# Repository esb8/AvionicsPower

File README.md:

## Overview

This project is a custom RP2040-based **Power Distribution Board**, designed for use in an avionics stack comprising three CAN-connected PCBs:  
- Sensor Board  
- Power Distribution Board **(this board)** 
- GPS Board

The system is intended for **high-power model rocketry**, and this board’s primary role is to **distribute power** to the rest of the system while also managing essential subsystems such as communication, monitoring, and recovery signaling.

---

## 📡 PCB Features

- High-current 3.3 V synchronous buck converter (up to 3 A), operating at 1.5 MHz and ~95% efficiency  
- Low-noise LDO with 60 dB PSRR @ 100 Hz, delivering up to 500 mA at 3.3 V  
- Single-cell Li-ion/LiPo battery protection IC with over-voltage, under-voltage, and over-current protection  
- CAN controller and transceiver  
- RP2040 microcontroller  
- USB-C interface  
- Onboard status LEDs for buck converter, MCU status, and USB-C diagnostics  
- External 128 Mbit W25Q128JVS flash memory  
- MAX98357A I²S digital amplifier connected to a speaker for audible recovery

---

## ✅ PCB Design Criteria

This board was designed to meet the following system-level criteria:

- **Stable, low-noise 3.3 V rail** for analog/digital loads — supports up to 500 mA with minimal line/load regulation (target: ±0.1%)
- **High-current 3.3 V rail** capable of supplying up to 3 A to downstream PCBs
- **Battery protection** for a 1S LiPo cell, including self-recovery from under-voltage and short-circuit protection
- **CAN bus communication interface** to enable modular system design with multiple nodes
- **Audible recovery system** — implemented using the **MAX98357A I²S Class-D amplifier**, which drives a speaker directly from the RP2040 using digital audio

---

## 📷 Media

**Schematic**  

**PCB Layout**  

**3D Model**

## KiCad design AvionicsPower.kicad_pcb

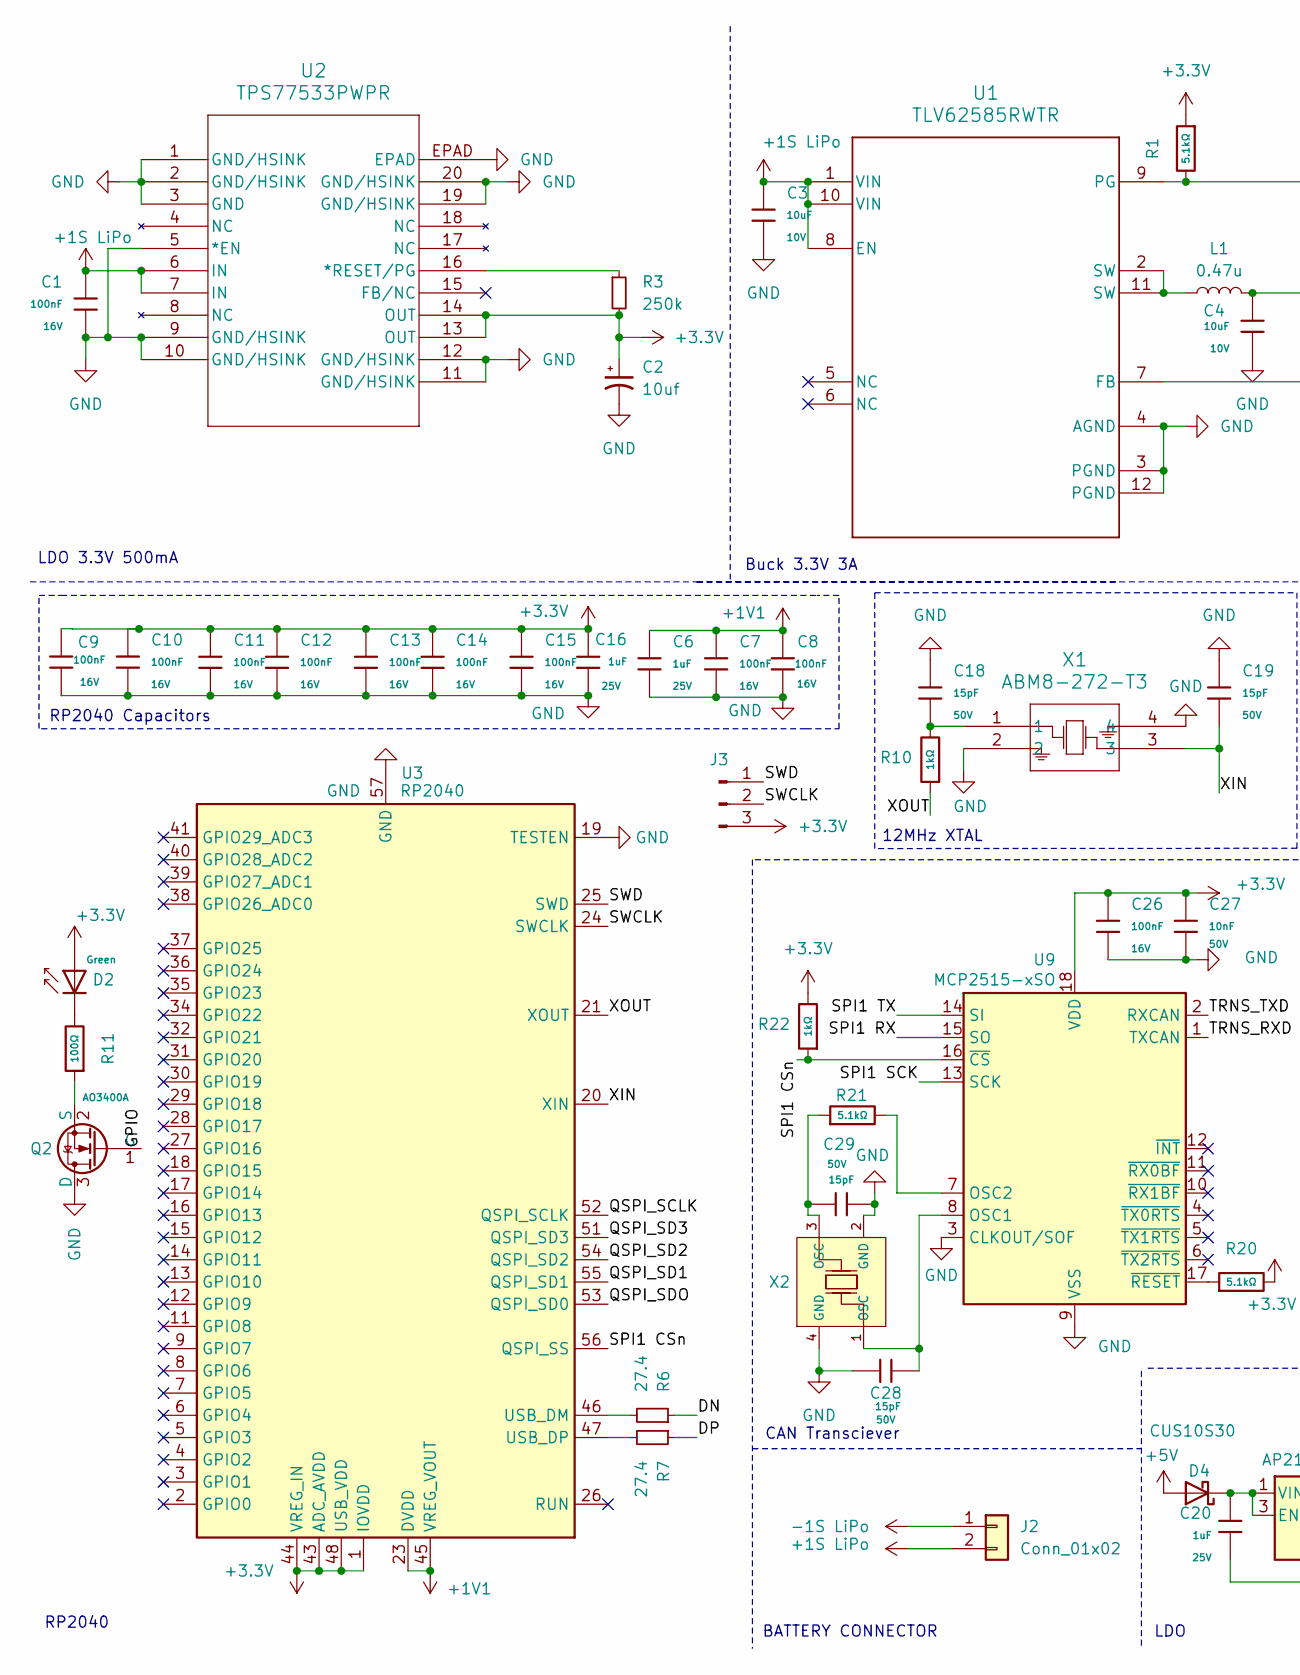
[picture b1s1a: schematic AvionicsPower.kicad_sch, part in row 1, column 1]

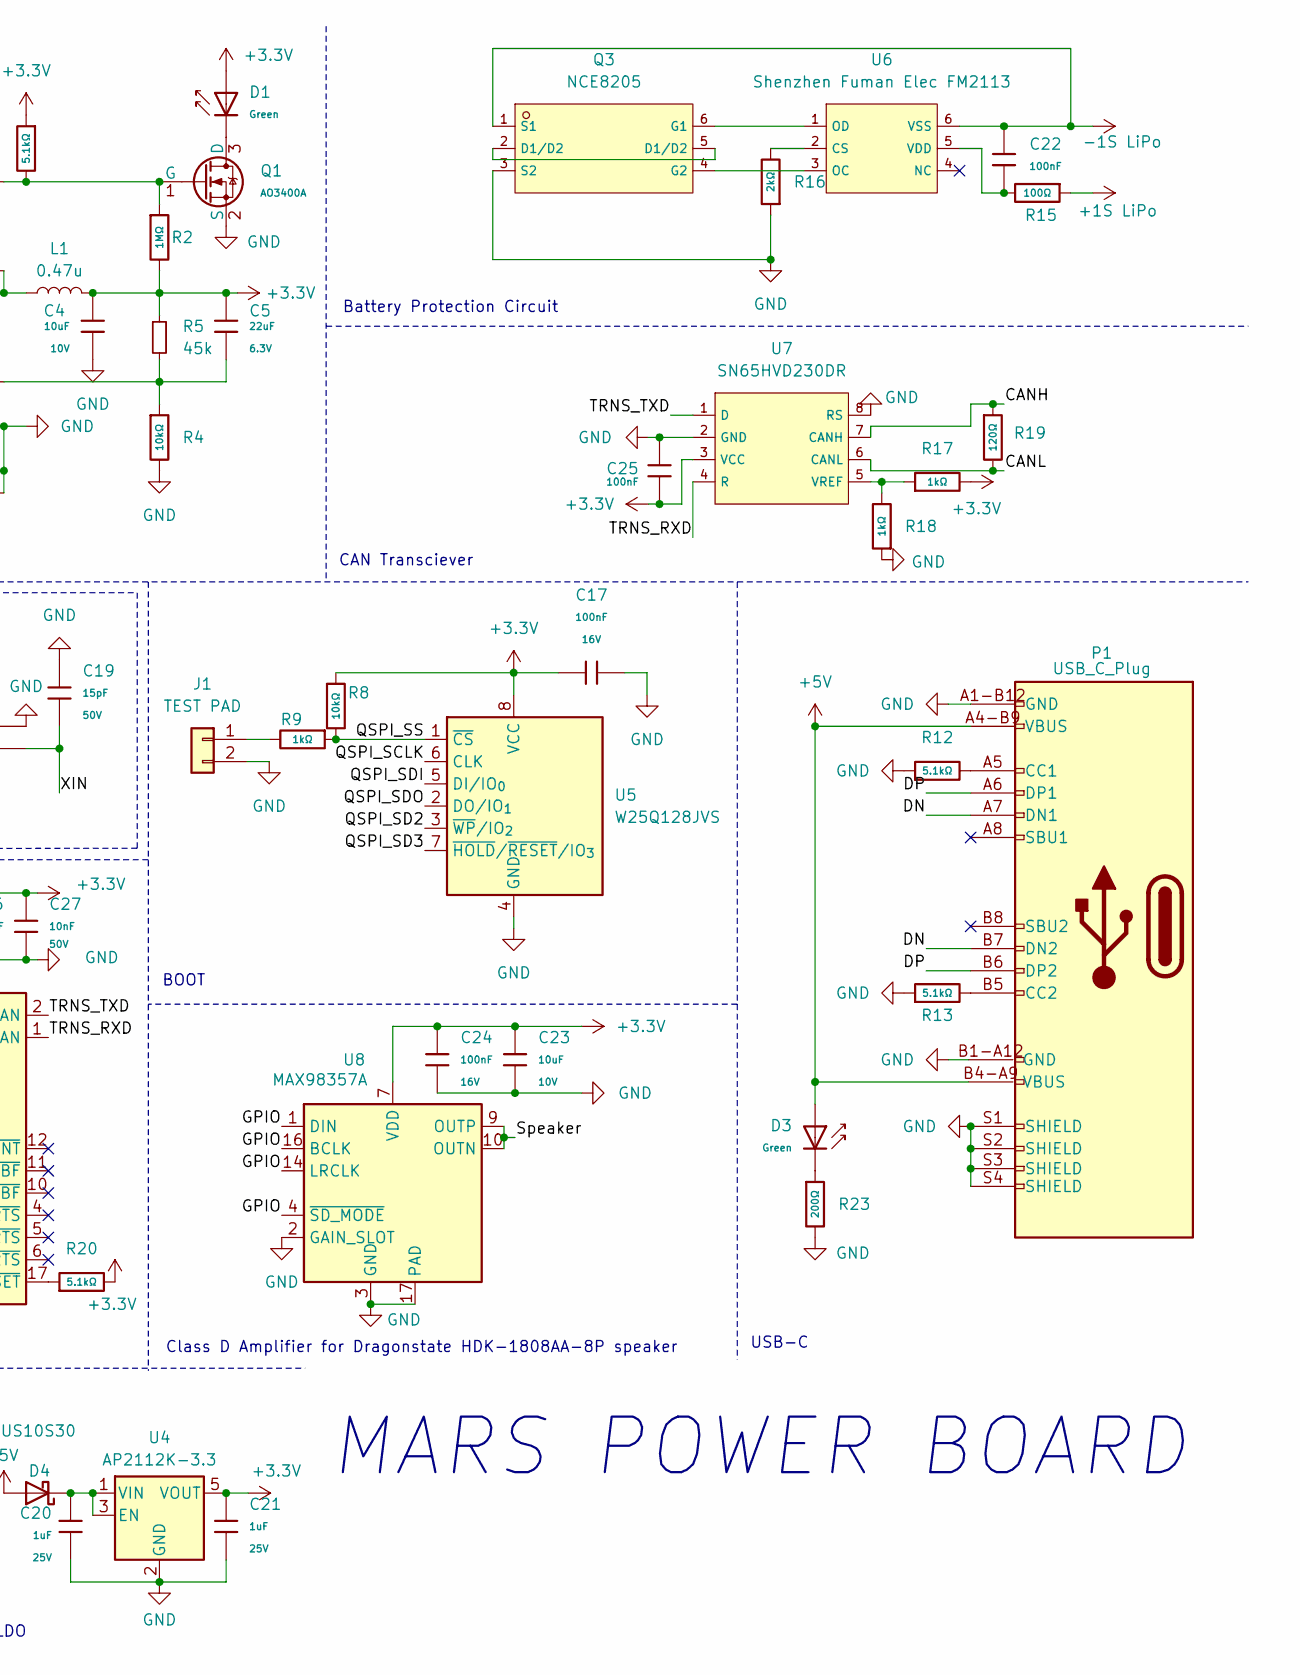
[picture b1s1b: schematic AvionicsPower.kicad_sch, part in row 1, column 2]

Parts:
C1, C7, C8, C9, C10, C11, C12, C13, C14, C15, C17, C22, C24, C25, C26: 100nF; C_0402; Voltage Rated 16V; Tolerance ±10%; Part CL05B104KO5NNNC; LCSC C1525
C2: 10uf; C_0805; LCSC C696821
C3, C4, C23: 10uF; C_0603; Voltage Rated 10V; Tolerance ±10%; Part CL10A106KP8NNNC; LCSC C19702
C5: 22uF; C_0603; Voltage Rated 6.3V; Tolerance ±20%; Part CL10A226MQ8NRNC; LCSC C59461
C6, C16, C20, C21: 1uF; C_0402; Voltage Rated 25V; Tolerance ±10%; Part CL05A105KA5NQNC; LCSC C52923
C18, C19, C28, C29: 15pF; C_0402; Voltage Rated 50V; Tolerance ±5%; Part 0402CG150J500NT; LCSC C1548
C27: 10nF; C_0402; Voltage Rated 50V; Tolerance ±10%; Part CL05B103KB5NNNC; LCSC C15195
D1, D2, D3: Green; D_0805; Part KT-0805G; LCSC C2297
D4: CUS10S30; D_SOD-323; LCSC C146335
J1: TEST PAD
J2: Conn_01x02; AMASS_XT60PW-M_1x02_P7.20mm_Horizontal; LCSC C131337
J3: Conn_01x03_Pin
L1: 0.47u
P1: USB_C_Plug; USB_C_Receptacle_GCT_USB4105-xx-A_16P_TopMnt_Horizontal
Q1, Q2: AO3400A; Q_SOT-23; Part AO3400A; LCSC C20917
Q3: NCE8205; SOT-23-6_L2.9-W1.6-P0.95-LS2.8-BR; LCSC C502858
R1, R12, R13, R20, R21: 5.1kΩ; R_0402_1005Metric; Overload Voltage (Max) 50V; Tolerance ±1%; Part 0402WGF5101TCE; LCSC C25905
R2: 1MΩ; R_0603_1608Metric; Overload Voltage (Max) 75V; Tolerance ±1%; Part 0603WAF1004T5E; LCSC C22935
R3: 250k; R_1206; LCSC C2828893
R4: 10kΩ; R_0805; Overload Voltage (Max) 150V; Tolerance ±1%; Part 0805W8F1002T5E; LCSC C17414
R5: 45k
R6, R7: 27.4; C_0402_1005Metric; LCSC C850920
R8: 10kΩ; R_0402_1005Metric; Overload Voltage (Max) 50V; Tolerance ±1%; Part 0402WGF1002TCE; LCSC C25744
R9, R10, R17, R18, R22: 1kΩ; R_0402_1005Metric; Overload Voltage (Max) 50V; Tolerance ±1%; Part 0402WGF1001TCE; LCSC C11702
R11, R15: 100Ω; R_0402_1005Metric; Overload Voltage (Max) 50V; Tolerance ±1%; Part 0402WGF1000TCE; LCSC C25076
R16: 2kΩ; R_0402_1005Metric; Overload Voltage (Max) 50V; Tolerance ±1%; Part 0402WGF2001TCE; LCSC C4109
R19: 120Ω; R_0402_1005Metric; Overload Voltage (Max) 50V; Tolerance ±1%; Part 0402WGF1200TCE; LCSC C25079
R23: 200Ω; R_0402; Overload Voltage (Max) 50V; Tolerance ±1%; Part 0402WGF2000TCE; LCSC C25087
U1: TLV62585RWTR; RWT0012A
U2: TPS77533PWPR; PWP20_3P38X2P4
U3: RP2040; QFN-56-1EP_7x7mm_P0.4mm_EP3.2x3.2mm
U4: AP2112K-3.3; SOT-23-5
U5: W25Q128JVS; SOIC-8_5.3x5.3mm_P1.27mm
U6: Shenzhen Fuman Elec FM2113; SOT-23-6_L2.9-W1.6-P0.95-LS2.8-BL; LCSC C2832124
U7: SN65HVD230DR; SOIC-8_L4.9-W3.9-P1.27-LS6.0-BL; Supply Voltage 3V~3.6V; Part SN65HVD230DR; LCSC C12084
U8: MAX98357A; TQFN-16-1EP_3x3mm_P0.5mm_EP1.23x1.23mm
U9: MCP2515-xSO; QFN-20-1EP_4x4mm_P0.5mm_EP2.5x2.5mm
X1: ABM8-272-T3; Crystal_SMD_3225-4Pin_3.2x2.5mm
X2: X322512MSB4SI; CRYSTAL-SMD_4P-L3.2-W2.5-BL; Frequency Tolerance ±10ppm; Part X322512MSB4SI; LCSC C9002

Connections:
+1S LiPo: C1.1, C3.1, J2.2, R15.1, U1.1 (VIN), U1.8 (EN), U1.10 (VIN), U2.6 (IN), U2.7 (IN)
+1V1: C6.1, C7.1, C8.1, U3.23 (DVDD), U3.45 (VREG_VOUT), U3.50 (DVDD)
+3.3V: C2.1, C4.1, C5.1, C9.1, C10.1, C11.1, C12.1, C13.1, C14.1, C15.1, C16.1, C17.1, C21.1, C23.1, C24.1, C25.2, C26.1, C27.1, D1.2, D2.2, J3.3, L1.2, R1.1, R2.2, R3.2, R5.1, R8.1, R17.2, R20.2, R22.2, U2.13 (OUT), U2.14 (OUT), U3.1 (IOVDD), U3.10 (IOVDD), U3.22 (IOVDD), U3.33 (IOVDD), U3.42 (IOVDD), U3.43 (ADC_AVDD), U3.44 (VREG_IN), U3.48 (USB_VDD), U3.49 (IOVDD), U4.5 (VOUT), U5.8 (VCC), U7.3 (VCC), U8.7 (VDD), U8.8 (VDD), U9.18 (VDD)
+5V: D3.2, D4.2 (A), P1.A4-B9 (VBUS), P1.B4-A9 (VBUS)
-1S LiPo: C22.1, J2.1, Q3.1 (S1), U6.6 (VSS)
/CANH: R19.1, U7.7 (CANH)
/CANL: R19.2, U7.6 (CANL)
/DN: P1.A7 (DN1), P1.B7 (DN2), R6.1
/DP: P1.A6 (DP1), P1.B6 (DP2), R7.1
/GPIO: Q2.1 (G), U8.1 (DIN), U8.4 (~SD_MODE), U8.14 (LRCLK), U8.16 (BCLK)
/QSPI_SCLK: U3.52 (QSPI_SCLK), U5.6 (CLK)
/QSPI_SD1: U3.55 (QSPI_SD1)
/QSPI_SD2: U3.54 (QSPI_SD2), U5.3 (~WP/IO_{2})
/QSPI_SD3: U3.51 (QSPI_SD3), U5.7 (~HOLD/~RESET/IO_{3})
/QSPI_SDI: U5.5 (DI/IO_{0})
/QSPI_SDO: U3.53 (QSPI_SD0), U5.2 (DO/IO_{1})
/QSPI_SS: R8.2, R9.1, U5.1 (~CS)
/SPI1 CSn: R22.1, U3.56 (QSPI_SS), U9.16 (~CS)
/SPI1 RX: U9.15 (SO)
/SPI1 SCK: U9.13 (SCK)
/SPI1 TX: U9.14 (SI)
/SWCLK: J3.2, U3.24 (SWCLK)
/SWD: J3.1, U3.25 (SWD)
/Speaker: U8.9 (OUTP), U8.10 (OUTN)
/TRNS_RXD: U7.4 (R), U9.1 (TXCAN)
/TRNS_TXD: U7.1 (D), U9.2 (RXCAN)
/XIN: C19.2, U3.20 (XIN), X1.3
/XOUT: R10.1, U3.21 (XOUT)
GND: C1.2, C2.2, C3.2, C4.2, C6.2, C7.2, C8.2, C9.2, C10.2, C11.2, C12.2, C13.2, C14.2, C15.2, C16.2, C17.2, C18.1, C19.1, C20.1, C21.2, C23.2, C24.2, C25.1, C26.2, C27.2, C28.1, C29.1, J1.2, P1.A1-B12 (GND), P1.B1-A12 (GND), P1.S1 (SHIELD), P1.S2 (SHIELD), P1.S3 (SHIELD), P1.S4 (SHIELD), Q1.2 (S), Q2.3 (D), Q3.3 (S2), R4.2, R12.1, R13.1, R16.1, R18.1, R23.2, U1.3 (PGND), U1.4 (AGND), U1.12 (PGND), U2.1 (GND/HSINK), U2.2 (GND/HSINK), U2.3 (GND), U2.5 (*EN), U2.9 (GND/HSINK), U2.10 (GND/HSINK), U2.11 (GND/HSINK), U2.12 (GND/HSINK), U2.19 (GND/HSINK), U2.20 (GND/HSINK), U2.EPAD, U3.19 (TESTEN), U3.57 (GND), U4.2 (GND), U5.4 (GND), U7.2 (GND), U7.8 (RS), U8.2 (GAIN_SLOT), U8.3 (GND), U8.11 (GND), U8.15 (GND), U8.17 (PAD), U9.3 (CLKOUT/SOF), U9.9 (VSS), X1.2, X1.4, X2.2 (GND), X2.4 (GND)
unnamed: C18.2, R10.2, X1.1
unnamed: C29.2, R21.1, X2.3 (OSC)
unnamed: D2.1, R11.2
unnamed: D3.1, R23.1
unnamed: C20.2, D4.1 (K), U4.1 (VIN), U4.3 (EN)
unnamed: J1.1, R9.2
unnamed: L1.1, U1.2 (SW), U1.11 (SW)
unnamed: P1.A5 (CC1), R12.2
unnamed: P1.B5 (CC2), R13.2
unnamed: D1.1, Q1.3 (D)
unnamed: Q1.1 (G), R1.2, R2.1, U1.9 (PG)
unnamed: Q2.2 (S), R11.1
unnamed: Q3.2 (D1/D2), Q3.5 (D1/D2)
unnamed: Q3.6 (G1), U6.1 (OD)
unnamed: Q3.4 (G2), U6.3 (OC)
unnamed: C5.2, R4.1, R5.2, U1.7 (FB)
unnamed: R3.1, U2.16 (*RESET/PG)
unnamed: R6.2, U3.46 (USB_DM)
unnamed: R7.2, U3.47 (USB_DP)
unnamed: R16.2, U6.2 (CS)
unnamed: C22.2, R15.2, U6.5 (VDD)
unnamed: R17.1, R18.2, U7.5 (VREF)
unnamed: C28.2, U9.8 (OSC1), X2.1 (OSC)
unnamed: R21.2, U9.7 (OSC2)
unnamed: R20.1, U9.17 (~RESET)

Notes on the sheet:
LDO
RP2040 Capacitors
MARS POWER BOARD
CAN Transciever
BATTERY CONNECTOR
BOOT
RP2040
12MHz XTAL
LDO 3.3V 500mA
USB-C
Class D Amplifier for Dragonstate HDK-1808AA-8P speaker
Battery Protection Circuit
Buck 3.3V 3A

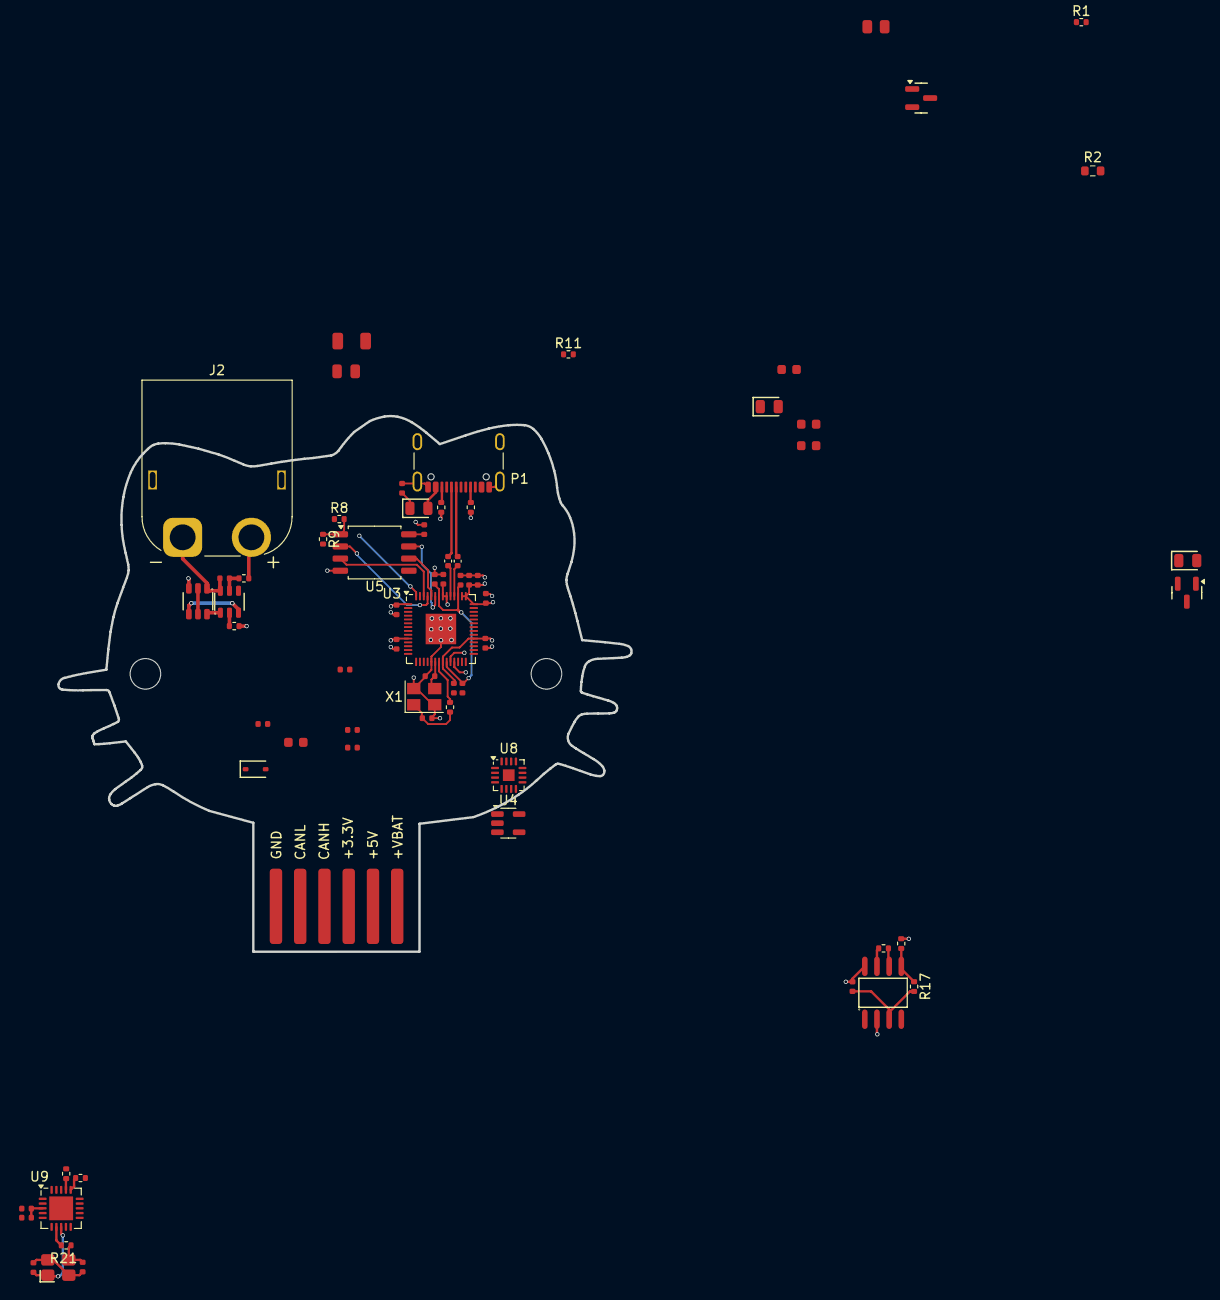
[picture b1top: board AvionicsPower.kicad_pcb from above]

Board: 2 copper layers, 60.0 x 56.1 mm, 68 parts (0 on the bottom side), 44 nets.

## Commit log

2025-07-03 Added LDO
2025-07-04 Added Buck Converter
2025-07-04 Added USB-C Connector, Added LDO, Added RP2040, Added Debug LEDs
2025-07-05 Added Battery Management IC
2025-07-05 Added Class D Amplifier and Speaker
2025-07-05 Added CAN Controller and Transciever, finalized schematic
2025-07-30 Began PCB Layout
2025-08-01 basic layout
2025-08-02 Finalized PCB layout.
2025-08-04 Changed connector, passed DRC, finalized PCB design
